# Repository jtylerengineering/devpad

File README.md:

# DevPad

## Description

This Devpad is a macropad designed around softwares I use when I do game development. It is powered by a SEEED Studio Xiao ESP32 C3 and CircuitPython. The software used is displayed on a 0.96 inch OLED display.

## Requirements

### Needed Components
| Part                 | Unit Amount | Unit Price | Net Price | Link                                                                                                                                                                                                                                                                                                                                                                                                                                                                                                                                                                                                                                                                  |
|----------------------|-------------|------------|-----------|-----------------------------------------------------------------------------------------------------------------------------------------------------------------------------------------------------------------------------------------------------------------------------------------------------------------------------------------------------------------------------------------------------------------------------------------------------------------------------------------------------------------------------------------------------------------------------------------------------------------------------------------------------------------------|
| 0.96 in OLED Display | $1.00       | $2.82      | 2.82      | https://www.aliexpress.us/item/3256805954920554.html?spm=a2g0o.cart.0.0.724038daQ3JUGJ&mp=1&pdp_npi=6%40dis%21USD%21USD+2.78%21USD+2.36%21%21USD+2.36%21%21%21%402101c68a17938389322556417e0f8e%2112000035944225406%21ct%21US%218282019388%21%211%210%21&_gl=1*8bl6l4*_gcl_au*NTc0MTAzMTgxLjE3OTM4MzU4NTU.*_ga*MjEyNDg2ODk1MC4xNzkzODM1ODU1*_ga_VED1YSGNC7*czE3OTM4MzU4NTUkbzEkZzEkdDE3OTM4Mzg5MzIkajI2JGwwJGgw&gatewayAdapt=glo2usa                                                                                                                                                                                                                                  |
| Keyboard Switches    | $1.00       | $5.81      | 5.81      | https://www.aliexpress.us/item/2255800623836900.html?spm=a2g0o.productlist.main.7.1c7642e60O5Q20&algo_pvid=8fdfb098-0e18-4200-a158-4d687397b14b&algo_exp_id=8fdfb098-0e18-4200-a158-4d687397b14b-6&pdp_ext_f=%7B%22order%22%3A%22129%22%2C%22eval%22%3A%221%22%2C%22fromPage%22%3A%22search%22%7D&pdp_npi=6%40dis%21USD%215.81%211.09%21%21%215.81%211.09%21%402101ea8f17939929003795901e07c1%2110000008113839980%21sea%21US%218282019388%21ABX%211%210%21n_tag%3A-29910%3Bd%3A601afdd8%3Bm03_new_user%3A-29895%3BpisId%3A5000000218165389&curPageLogUid=EiToXPOyKv3L&utparam-url=scene%3Asearch%7Cquery_from%3A%7Cx_object_id%3A4000810151652%7C_p_origin_prod%3A    |
| Xiao ESP32 C3        | $1.00       | $8.76      | 8.76      | https://www.aliexpress.us/item/3256806641821574.html?spm=a2g0o.productlist.main.2.28ab421cMq7NOX&algo_pvid=cb019987-8f1f-4f64-9d3b-c238b64d609a&algo_exp_id=cb019987-8f1f-4f64-9d3b-c238b64d609a-1&pdp_ext_f=%7B%22order%22%3A%2250%22%2C%22eval%22%3A%221%22%2C%22fromPage%22%3A%22search%22%7D&pdp_npi=6%40dis%21USD%218.76%211.09%21%21%2158.09%217.23%21%402101d2e717939912963321630e1065%2112000047891524753%21sea%21US%218282019388%21ABX%211%210%21n_tag%3A-29910%3Bd%3A601afdd8%3Bm03_new_user%3A-29895%3BpisId%3A5000000218165389&curPageLogUid=4UV4BPsLIaC9&utparam-url=scene%3Asearch%7Cquery_from%3A%7Cx_object_id%3A1005006828136326%7C_p_origin_prod%3A |
| EC11 Rotary Encoder  | $1.00       | $2.29      | 2.29      | https://www.aliexpress.us/item/3256813007942184.html?spm=a2g0o.cart.0.0.17c538da3eu4Ri&mp=1&pdp_npi=6%40dis%21USD%21USD+2.29%21USD+2.02%21%21USD+2.02%21%21%21%402103081117939914664448460e0c82%2112000060523754199%21ct%21US%218282019388%21%211%210%21&_gl=1*1iu255p*_gcl_au*NTc0MTAzMTgxLjE3OTM4MzU4NTU.*_ga*MjEyNDg2ODk1MC4xNzkzODM1ODU1*_ga_VED1YSGNC7*czE3OTM5OTEyNjUkbzMkZzEkdDE3OTM5OTE0ODEkajE1JGwwJGgw&gatewayAdapt=glo2usa                                                                                                                                                                                                                                 |
| Diodes               | $1.00       | $1.69      | 1.69      | https://www.aliexpress.us/item/2255799869438855.html?spm=a2g0o.productlist.main.3.b4423fccClvMTZ&algo_pvid=06772ee0-8a3e-42bc-baec-d36982b0394a&algo_exp_id=06772ee0-8a3e-42bc-baec-d36982b0394a-2&pdp_ext_f=%7B%22order%22%3A%22104%22%2C%22eval%22%3A%221%22%2C%22fromPage%22%3A%22search%22%7D&pdp_npi=6%40dis%21USD%211.69%211.09%21%21%211.69%211.09%21%402101e81117939918020221017e0f4a%2110000000124200168%21sea%21US%218282019388%21ABX%211%210%21n_tag%3A-29910%3Bd%3A601afdd8%3Bm03_new_user%3A-29895%3BpisId%3A5000000218165384&curPageLogUid=6qzAvyRVgbXp&utparam-url=scene%3Asearch%7Cquery_from%3A%7Cx_object_id%3A4000055753607%7C_p_origin_prod%3A    |
| PCB                  | $1.00       | $8.70      | $8.70     | https://jlcpcb.com/                                                                                                                                                                                                                                                                                                                                                                                                                                                                                                                                                                                                                                                   |
| Shipping/ Tax        | N/A         | N/A        | $3.30     | N/A                                                                                                                                                                                                                                                                                                                                                                                                                                                                                                                                                                                                                                                                   |
| Total                | $27.56      |            |           |                                                                                                                                                                                                                                                                                                                                                                                                                                                                                                                                                                                                                                                                       |                                                                                                                                                                                                                                                                                                                                                                                                                                                                                                                                                                                                                                                     
### Tools
Other than the above parts, you will also need:
1. A set of soldering tools (iron, helping hands, solder)
2. A 3D Printer and filament for the case/keycaps
3. A computer
4. a clean workspace

### Software 
You will need to have <a href="https://docs.circuitpython.org/en/latest/README.html">Circuit Python</a> installed. 

## Assembly instructions

A full detailed set of instructions will be posted when the project is built (to get pictures).

## Quick Links
<a href="https://cad.onshape.com/documents/498155ee3d1338c09480fffd/w/4b6f6ad77c90c70c54e2afba/e/de59654b164c33272e9a1a9b?renderMode=0&uiState=6af0d49d5a2e1992e1d22ae4">Onshape Document</a>

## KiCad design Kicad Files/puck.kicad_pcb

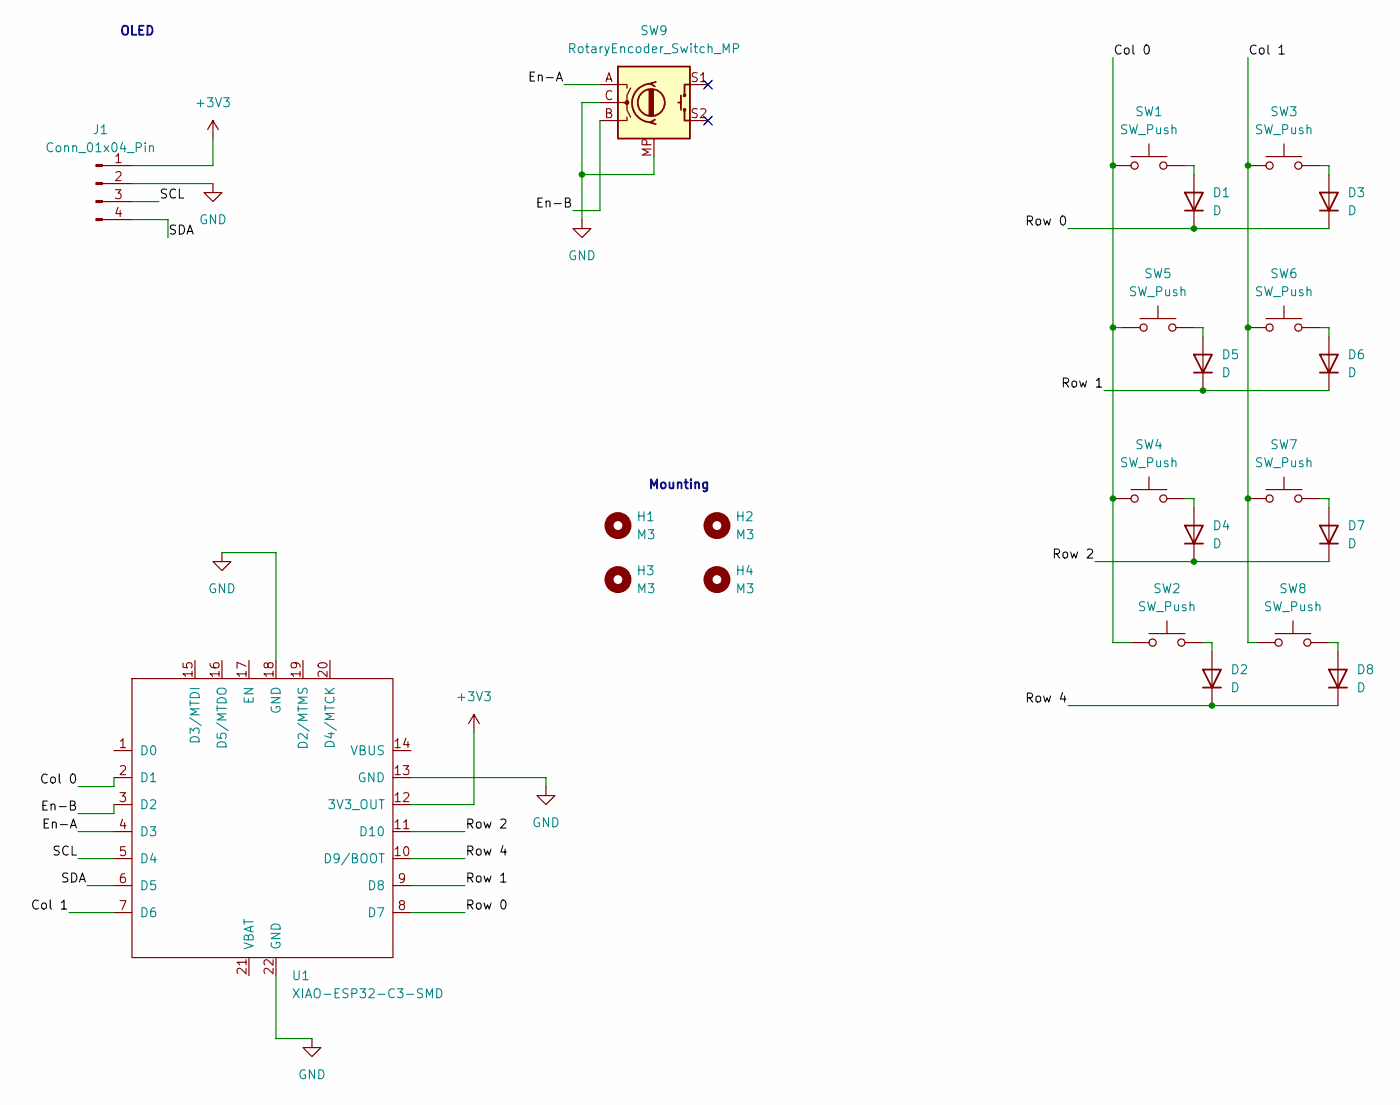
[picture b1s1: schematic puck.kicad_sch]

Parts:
D1, D2, D3, D4, D5, D6, D7, D8: D; D_SOD-123
H1, H2, H3, H4: M3; MountingHole_3.2mm_M3
J1: Conn_01x04_Pin; PinHeader_1x04_P2.54mm_Vertical
SW1, SW2, SW3, SW4, SW5, SW6, SW7, SW8: SW_Push; SW_Cherry_MX_1.00u_PCB
SW9: RotaryEncoder_Switch_MP; RotaryEncoder_Alps_EC11E-Switch_Vertical_H20mm
U1: XIAO-ESP32-C3-SMD; XIAO-ESP32-C3-DIP-SMD

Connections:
+3V3: J1.1, U1.12 (3V3_OUT)
/Col 0: SW1.1, SW2.1, SW4.1, SW5.1, U1.2 (D1)
/Col 1: SW3.1, SW6.1, SW7.1, SW8.1, U1.7 (D6)
/En-A: SW9.A, U1.4 (D3)
/En-B: SW9.B, U1.3 (D2)
/Row 0: D1.1 (K), D3.1 (K), U1.8 (D7)
/Row 1: D5.1 (K), D6.1 (K), U1.9 (D8)
/Row 2: D4.1 (K), D7.1 (K), U1.11 (D10)
/Row 4: D2.1 (K), D8.1 (K), U1.10 (D9/BOOT)
/SCL: J1.3, U1.5 (D4)
/SDA: J1.4, U1.6 (D5)
GND: J1.2, SW9.C, SW9.MP, U1.13 (GND), U1.18 (GND), U1.22 (GND)
unnamed: D1.2 (A), SW1.2
unnamed: D2.2 (A), SW2.2
unnamed: D3.2 (A), SW3.2
unnamed: D4.2 (A), SW4.2
unnamed: D5.2 (A), SW5.2
unnamed: D6.2 (A), SW6.2
unnamed: D7.2 (A), SW7.2
unnamed: D8.2 (A), SW8.2

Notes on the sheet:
Mounting
OLED

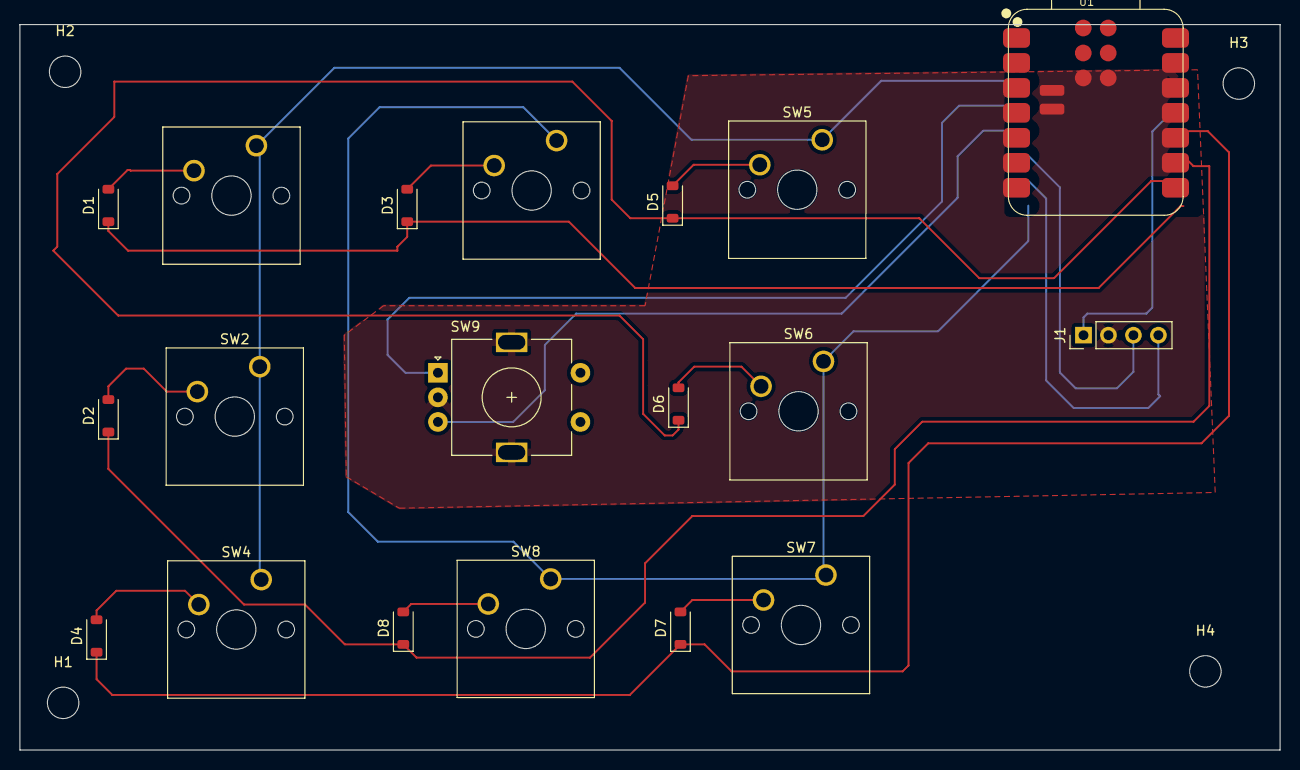
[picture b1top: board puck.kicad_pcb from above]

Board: 2 copper layers, 128.2 x 73.8 mm, 23 parts (0 on the bottom side), 20 nets.
